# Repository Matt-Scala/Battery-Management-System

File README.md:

## Members
Matthew Scala, Electrical Engineering
matthewscala3820@vt.edu 

## Mentor
Shane Wyman

## Current Status
Finished

## Project Overview
Create a 4-layer PCB BMS(Battery Management System) with voltage, current, temperature, and fault monitoring. Also, include active cell balancing.

## Educational Value Added

Batteries
Analog routing
SPI communication
Embedded systems
PCB Design 
Electronic Circuit Design

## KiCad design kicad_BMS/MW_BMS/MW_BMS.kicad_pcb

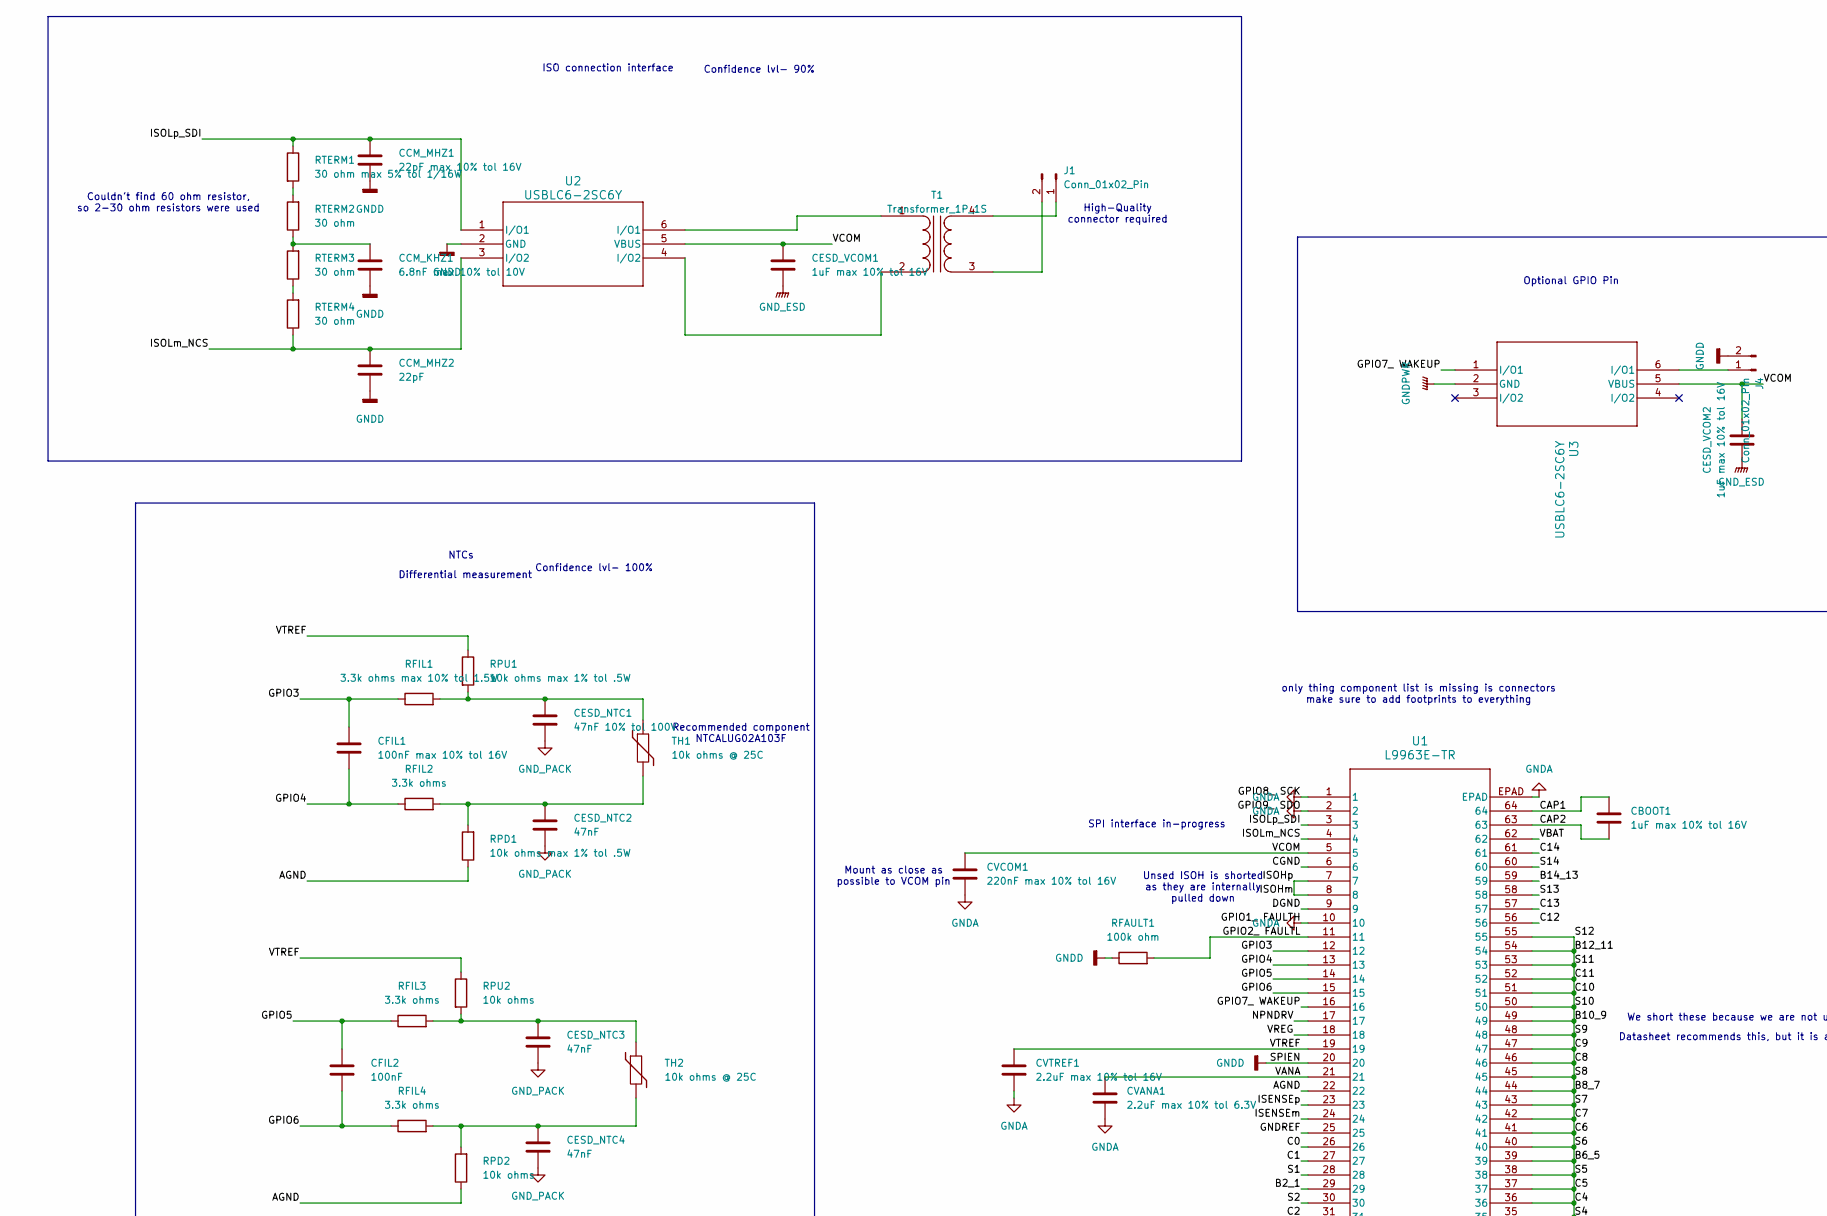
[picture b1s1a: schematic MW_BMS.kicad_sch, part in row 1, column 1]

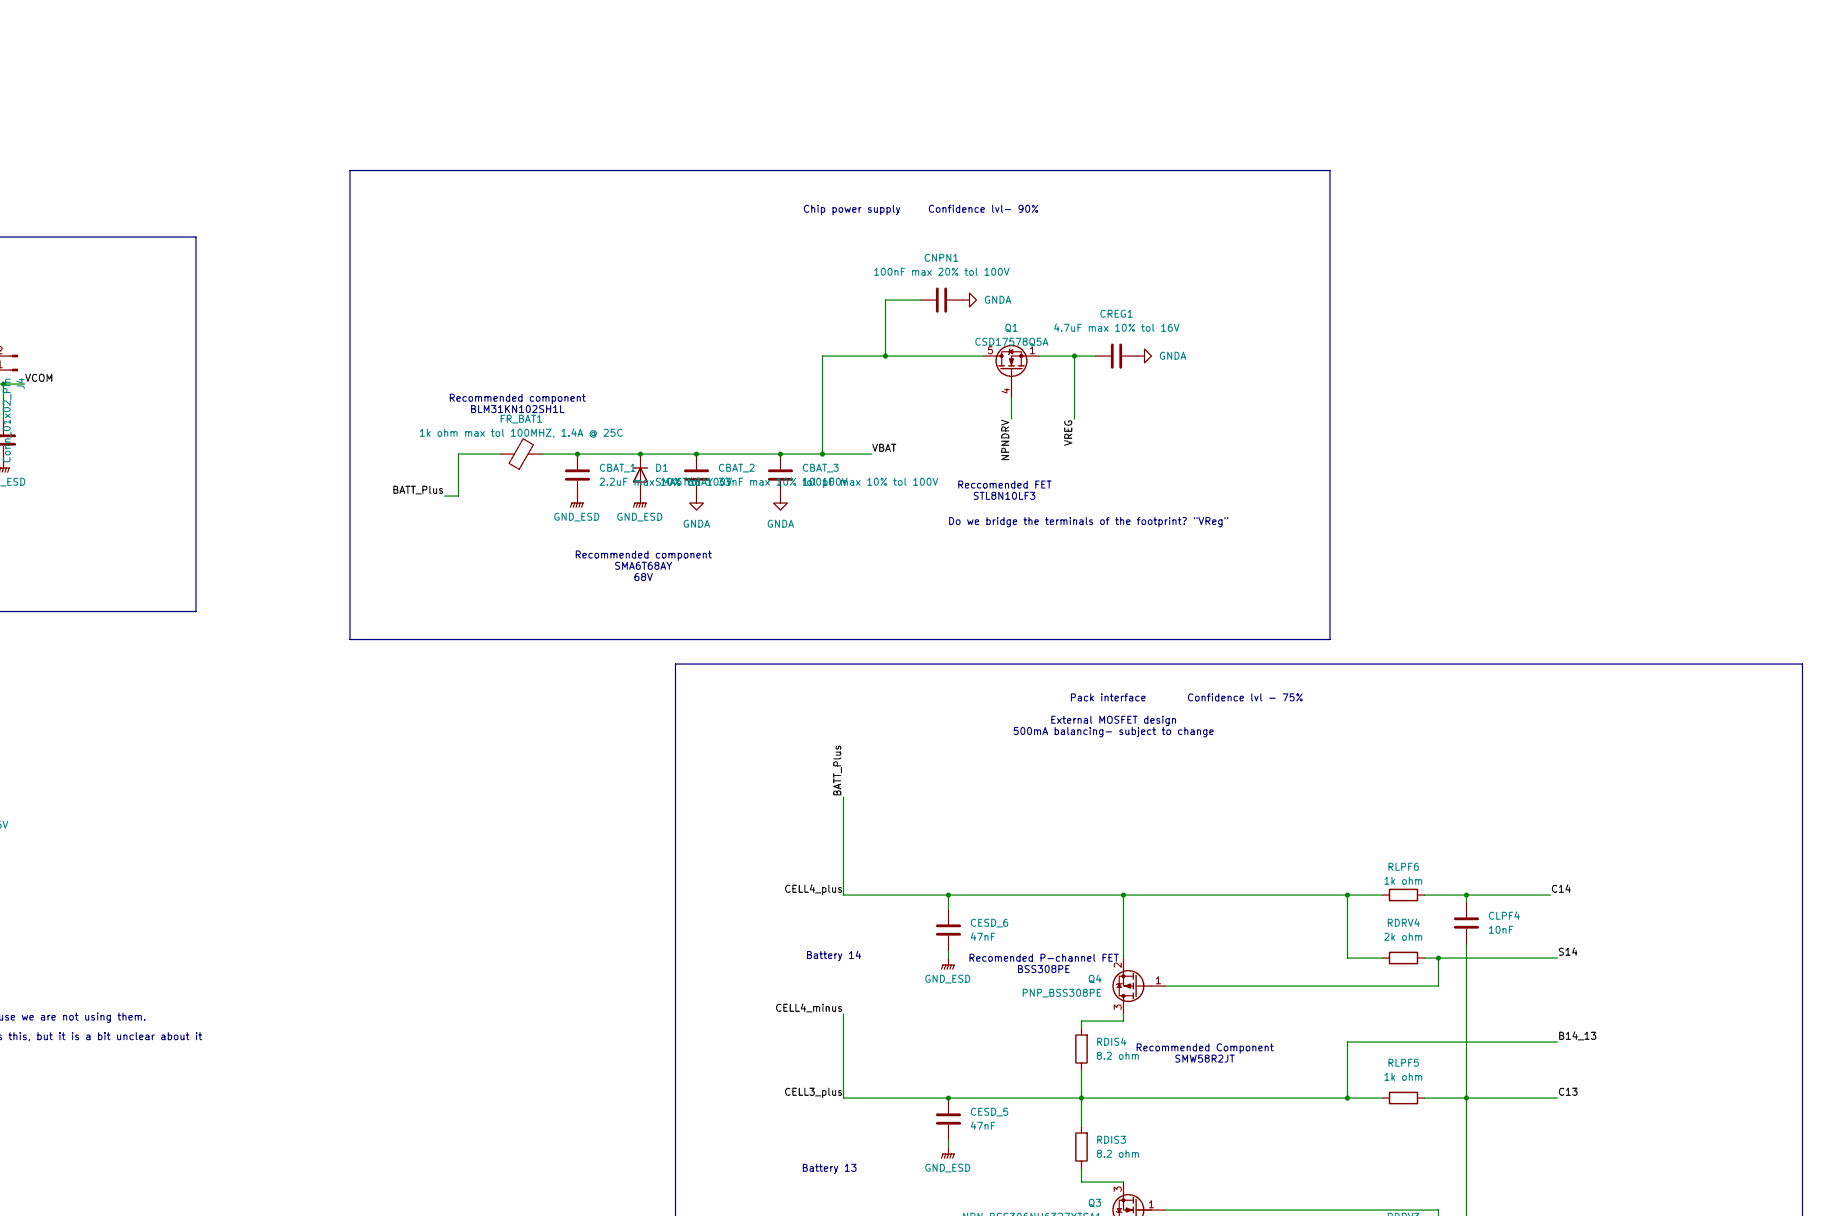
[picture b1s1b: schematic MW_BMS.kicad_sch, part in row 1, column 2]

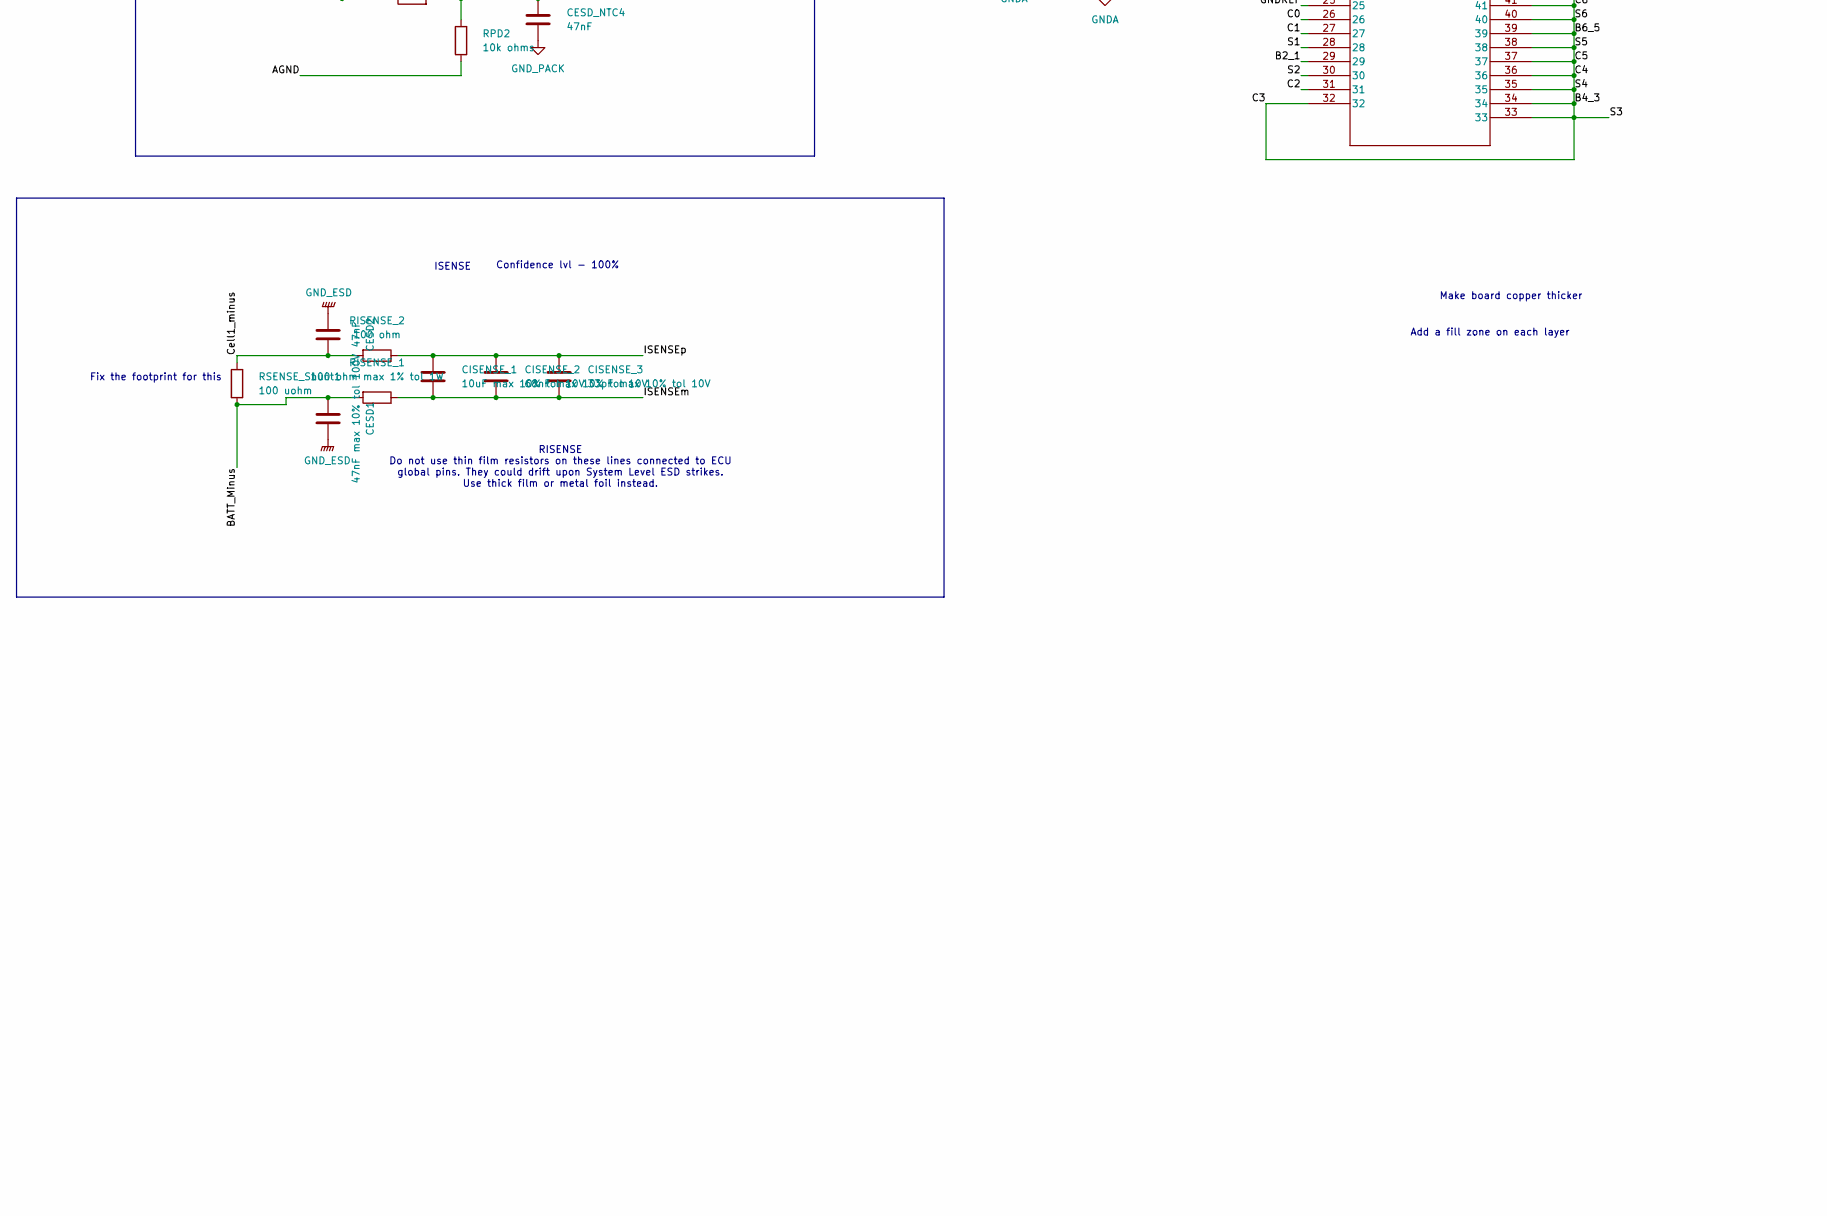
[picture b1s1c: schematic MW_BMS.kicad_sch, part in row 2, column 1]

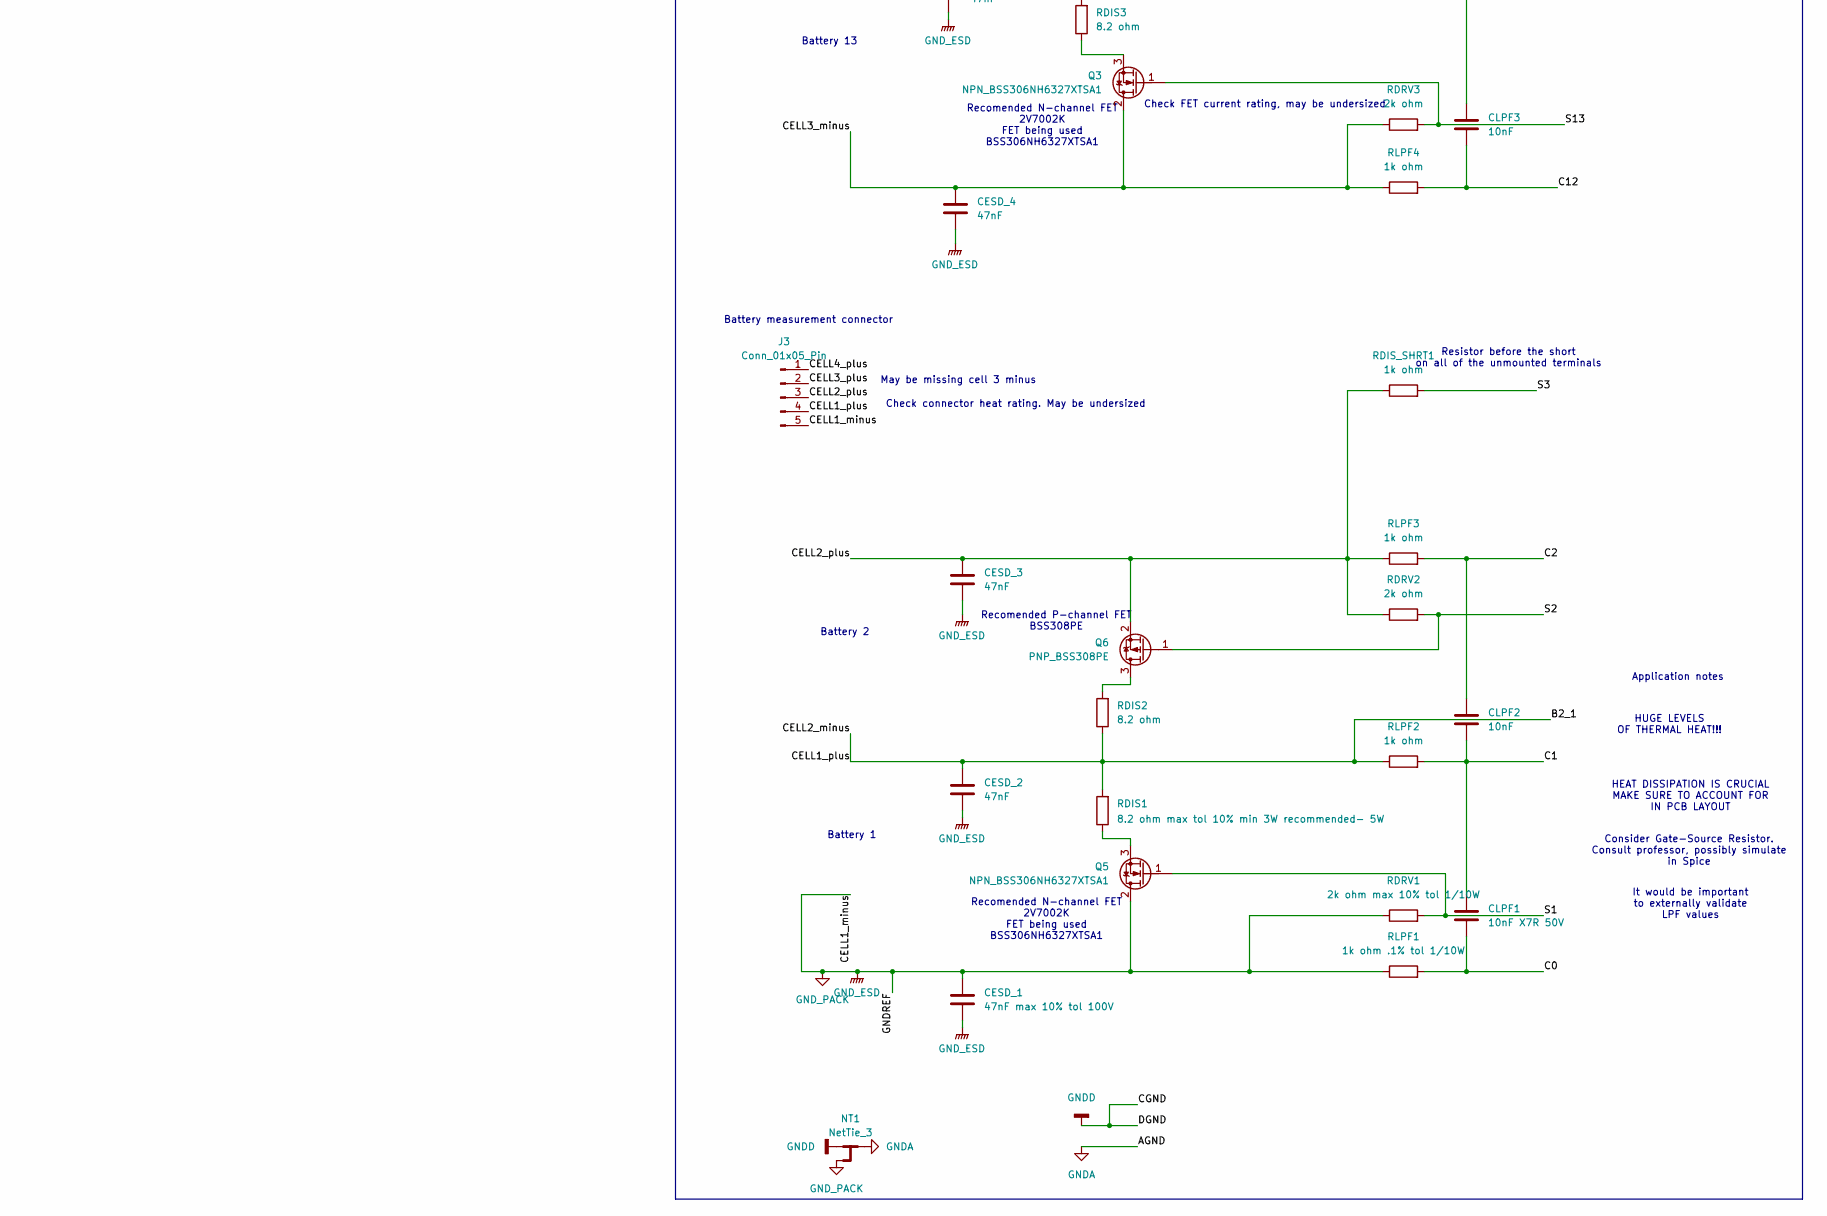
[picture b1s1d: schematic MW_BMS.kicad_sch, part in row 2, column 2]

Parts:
CBAT_1: 2.2uF max 10% tol 100V; C_1206_3216Metric
CBAT_2: 33nF max 10% tol 100V; C_0805_2012Metric
CBAT_3: 100pF max 10% tol 100V; C_0603_1608Metric
CBOOT1: 1uF max 10% tol 16V; C_0603_1608Metric
CCM_KHZ1: 6.8nF max 10% tol 10V; C_0603_1608Metric
CCM_MHZ1: 22pF max 10% tol 16V; C_0603_1608Metric
CCM_MHZ2: 22pF; C_0603_1608Metric
CESD1: 47nF max 10% tol 100V; C_0805_2012Metric
CESD2: 47nF; C_0805_2012Metric
CESD_1: 47nF max 10% tol 100V; C_0805_2012Metric
CESD_2, CESD_3, CESD_4, CESD_5, CESD_6: 47nF; C_0805_2012Metric
CESD_NTC1: 47nF 10% tol 100V; C_0805_2012Metric
CESD_NTC2, CESD_NTC3, CESD_NTC4: 47nF; C_0805_2012Metric
CESD_VCOM1, CESD_VCOM2: 1uF max 10% tol 16V; C_0805_2012Metric
CFIL1: 100nF max 10% tol 16V; C_0603_1608Metric
CFIL2: 100nF; C_0603_1608Metric
CISENSE_1: 10uF max 10% tol 10V; C_1206_3216Metric
CISENSE_2: 68nF max 10% tol 10V; C_0603_1608Metric
CISENSE_3: 33pF max 10% tol 10V; C_0603_1608Metric
CLPF1: 10nF X7R 50V; C_0402_1005Metric
CLPF2, CLPF3, CLPF4: 10nF; C_0402_1005Metric
CNPN1: 100nF max 20% tol 100V; C_0805_2012Metric
CREG1: 4.7uF max 10% tol 16V; C_0805_2012Metric
CVANA1: 2.2uF max 10% tol 6.3V; C_0805_2012Metric
CVCOM1: 220nF max 10% tol 16V; C_0603_1608Metric
CVTREF1: 2.2uF max 10% tol 16V; C_0805_2012Metric
D1: SMA6T68AY; D_SMA
FR_BAT1: 1k ohm max tol 100MHZ, 1.4A @ 25C; R_1206_3216Metric
J1, J4: Conn_01x02_Pin; JST_GH_BM02B-GHS-TBT_1x02-1MP_P1.25mm_Vertical
J3: Conn_01x05_Pin; JST_GH_BM05B-GHS-TBT_1x05-1MP_P1.25mm_Vertical
NT1: NetTie_3; NetTie-3_THT_Pad1.0mm
Q1: CSD17578Q5A; TRANS_STL60P4LLF6
Q3, Q5: NPN_BSS306NH6327XTSA1; TSOT-23
Q4, Q6: PNP_BSS308PE; TSOT-23
RDIS1: 8.2 ohm max tol 10% min 3W recommended- 5W; RES_SMF5_TYCO_TYC
RDIS2, RDIS3, RDIS4: 8.2 ohm; RES_SMF5_TYCO_TYC
RDIS_SHRT1: 1k ohm; R_0603_1608Metric
RDRV1: 2k ohm max 10% tol 1/10W; R_0603_1608Metric
RDRV2, RDRV3, RDRV4: 2k ohm; R_0603_1608Metric
RFAULT1: 100k ohm; R_0603_1608Metric
RFIL1: 3.3k ohms max 10% tol 1.5W; R_2512_6332Metric
RFIL2, RFIL3, RFIL4: 3.3k ohms; R_2512_6332Metric
RISENSE_1: 100 ohm max 1% tol 1W; R_2512_6332Metric
RISENSE_2: 100 ohm; R_2512_6332Metric
RLPF1: 1k ohm .1% tol 1/10W; R_0603_1608Metric
RLPF2, RLPF3, RLPF4, RLPF5, RLPF6: 1k ohm; R_0603_1608Metric
RPD1: 10k ohms max 1% tol .5W; R_1206_3216Metric
RPD2: 10k ohms; R_1206_3216Metric
RPU1: 10k ohms max 1% tol .5W; R_1206_3216Metric
RPU2: 10k ohms; R_1206_3216Metric
RSENSE_Shunt1: 100 uohm; Shunt
RTERM1: 30 ohm max 5% tol 1/16W; R_0402_1005Metric
RTERM2, RTERM3, RTERM4: 30 ohm; R_0402_1005Metric
T1: Transformer_1P_1S; Transformer
TH1, TH2: 10k ohms @ 25C; Thermistor
U1: L9963E-TR; TQFP_63E-TR_STM
U2, U3: USBLC6-2SC6Y; SOT23-6L_STM

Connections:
/B2_1: CESD_2.1, J3.4, RDIS1.2, RDIS2.1, RLPF2.1, U1.29
/B10_9: RDIS_SHRT1.2, U1.32, U1.33, U1.34, U1.35, U1.36, U1.37, U1.38, U1.39, U1.40, U1.41, U1.42, U1.43, U1.44, U1.45, U1.46, U1.47, U1.48, U1.49, U1.50, U1.51, U1.52, U1.53, U1.54, U1.55
/B14_13: CESD_5.1, J3.2, RDIS3.2, RDIS4.1, RLPF5.1, U1.59
/BATT_Minus: CESD1.1, RISENSE_1.2, RSENSE_Shunt1.2
/BATT_Plus: CESD_6.1, FR_BAT1.1, J3.1, Q4.2 (S), RDRV4.1, RLPF6.1
/C0: CLPF1.2, RLPF1.2, U1.26
/C1: CLPF1.1, CLPF2.2, RLPF2.2, U1.27
/C2: CLPF2.1, RLPF3.2, U1.31
/C12: CLPF3.2, RLPF4.2, U1.56
/C13: CLPF3.1, CLPF4.2, RLPF5.2, U1.57
/C14: CLPF4.1, RLPF6.2, U1.61
/CAP1: CBOOT1.1, U1.64
/CAP2: CBOOT1.2, U1.63
/Cell1_minus: CESD2.2, RISENSE_2.2, RSENSE_Shunt1.1
/GPIO2_ FAULTL: RFAULT1.2, U1.11
/GPIO3: CFIL1.1, RFIL1.1, U1.12
/GPIO4: CFIL1.2, RFIL2.1, U1.13
/GPIO5: CFIL2.1, RFIL3.1, U1.14
/GPIO6: CFIL2.2, RFIL4.1, U1.15
/GPIO7_ WAKEUP: U1.16, U3.1 (I/O1)
/ISENSEm: CISENSE_1.1, CISENSE_2.1, CISENSE_3.1, RISENSE_1.1, U1.24
/ISENSEp: CISENSE_1.2, CISENSE_2.2, CISENSE_3.2, RISENSE_2.1, U1.23
/ISOHm: U1.7, U1.8
/ISOLm_NCS: CCM_MHZ2.1, RTERM4.1, U1.4, U2.3 (I/O2)
/ISOLp_SDI: CCM_MHZ1.1, RTERM1.1, U1.3, U2.1 (I/O1)
/NPNDRV: Q1.4 (G), U1.17
/S1: Q5.1 (G), RDRV1.2, U1.28
/S2: Q6.1 (G), RDRV2.2, U1.30
/S13: Q3.1 (G), RDRV3.2, U1.58
/S14: Q4.1 (G), RDRV4.2, U1.60
/VANA: CVANA1.1, U1.21
/VBAT: CBAT_1.1, CBAT_2.1, CBAT_3.1, CNPN1.1, D1.1 (K), FR_BAT1.2, Q1.5 (D), Q1.7, Q1.8, U1.62
/VCOM: CESD_VCOM1.1, CESD_VCOM2.2, CVCOM1.1, U1.5, U2.5 (VBUS), U3.5 (VBUS)
/VREG: CREG1.1, Q1.1 (S), Q1.2 (S), Q1.3 (S), U1.18
/VTREF: CVTREF1.1, RPU1.1, RPU2.1, U1.19
GNDA: CBAT_2.2, CBAT_3.2, CNPN1.2, CREG1.2, CVANA1.2, CVCOM1.2, CVTREF1.2, NT1.2, RPD1.1, RPD2.1, U1.1, U1.2, U1.10, U1.22, U1.EPAD
GNDD: CCM_KHZ1.2, CCM_MHZ1.2, CCM_MHZ2.2, J4.2, NT1.1, RFAULT1.1, U1.6, U1.9, U1.20, U2.2 (GND)
GNDPWR: U3.2 (GND)
GND_ESD: CBAT_1.2, CESD1.2, CESD2.1, CESD_1.1, CESD_1.2, CESD_2.2, CESD_3.2, CESD_4.2, CESD_5.2, CESD_6.2, CESD_NTC1.2, CESD_NTC2.2, CESD_NTC3.2, CESD_NTC4.2, CESD_VCOM1.2, CESD_VCOM2.1, D1.2 (A), J3.5, NT1.3, Q5.2 (D), RDRV1.1, RLPF1.1, U1.25
unnamed: CCM_KHZ1.1, RTERM2.1, RTERM3.2
unnamed: CESD_NTC1.1, RFIL1.2, RPU1.2, TH1.1
unnamed: CESD_NTC2.1, RFIL2.2, RPD1.2, TH1.2
unnamed: CESD_NTC3.1, RFIL3.2, RPU2.2, TH2.1
unnamed: CESD_NTC4.1, RFIL4.2, RPD2.2, TH2.2
unnamed: J1.1, T1.4 (SB)
unnamed: J1.2, T1.3 (SA)
unnamed: J4.1, U3.6 (I/O1)
unnamed: Q3.3 (S), RDIS3.1
unnamed: Q4.3 (D), RDIS4.2
unnamed: Q5.3 (S), RDIS1.1
unnamed: Q6.3 (D), RDIS2.2
unnamed: RTERM1.2, RTERM2.2
unnamed: RTERM3.1, RTERM4.2
unnamed: T1.1 (AA), U2.6 (I/O1)
unnamed: T1.2 (AB), U2.4 (I/O2)

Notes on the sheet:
ISENSE
Unsed ISOH is shorted as they are internally pulled down
Confidence lvl- 100%
Datasheet recommends this, but it is a bit unclear about it
Couldn't find 60 ohm resistor, so 2-30 ohm resistors were used
Confidence lvl- 90%
We short these because we are not using them.
Recommended Component SMW58R2JT
It would be important to externally validate LPF values
Resistor before the short on all of the unmounted terminals
RISENSE Do not use thin film resistors on these lines connected to ECU global pins. They could drift upon System Level ESD strikes. Use thick film or metal foil instead.
ISO connection interface
Pack interface
Do we bridge the terminals of the footprint? "VReg"
Confidence lvl - 100%
Reccomended FET STL8N10LF3
Recommended component SMA6T68AY 68V
Battery 1
Recomended N-channel FET 2V7002K FET being used BSS306NH6327XTSA1
Check connector heat rating. May be undersized
Battery 13
HEAT DISSIPATION IS CRUCIAL MAKE SURE TO ACCOUNT FOR IN PCB LAYOUT
Confidence lvl - 75%
Application notes
Differential measurement
Recomended P-channel FET BSS308PE
SPI interface in-progress
Add a fill zone on each layer
Mount as close as possible to VCOM pin
Make board copper thicker
High-Quality connector required
Check FET current rating, may be undersized
Optional GPIO Pin
May be missing cell 3 minus
Recommended component NTCALUG02A103F
Chip power supply
Battery 2
Recommended component BLM31KN102SH1L
Battery 14
only thing component list is missing is connectors make sure to add footprints to everything

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
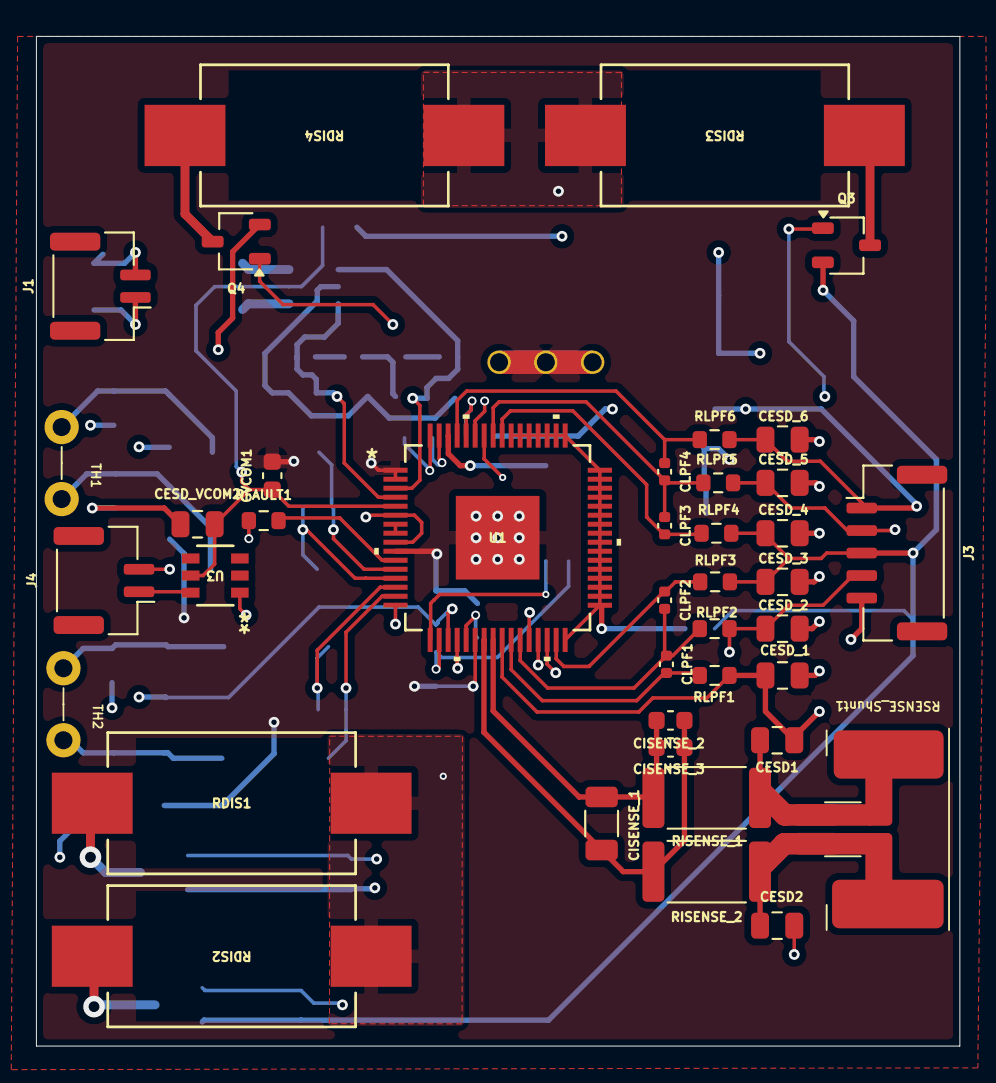
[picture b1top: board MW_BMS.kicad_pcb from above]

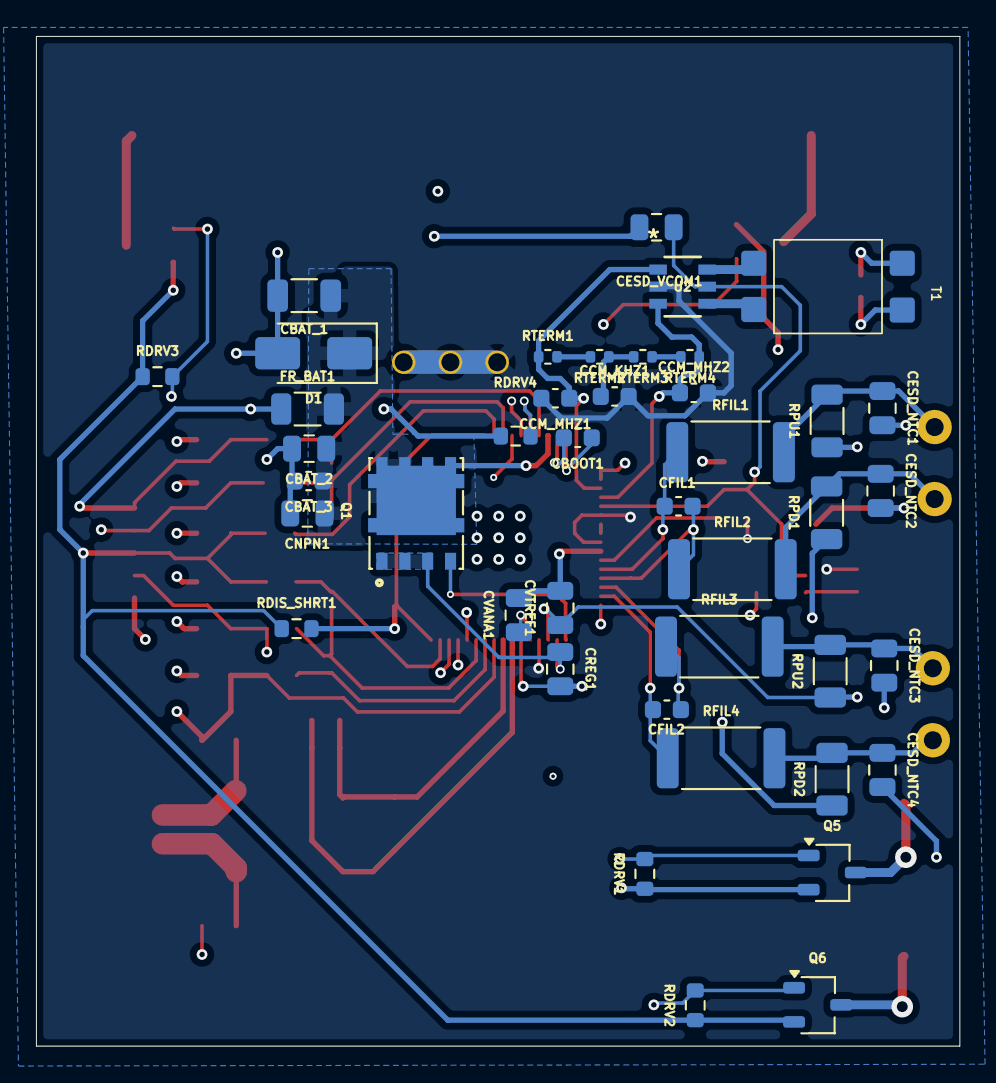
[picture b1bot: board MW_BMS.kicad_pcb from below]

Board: 4 copper layers, 51.3 x 56.1 mm, 83 parts (42 on the bottom side), 55 nets.

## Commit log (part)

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2026-03-08 Revise project overview and team information
    Updated project details and team members in README.
2026-04-26 BMS_Chip_Files
2026-04-26 more files
2026-04-27 most_routing_done
2026-04-27 more_improvements
    just need ground planes, and to make a decision about cell3_minus
2026-04-27 backups
2026-05-19 fixed spi
2026-05-31 ground connected
2026-05-31 closed kicad on laptop
